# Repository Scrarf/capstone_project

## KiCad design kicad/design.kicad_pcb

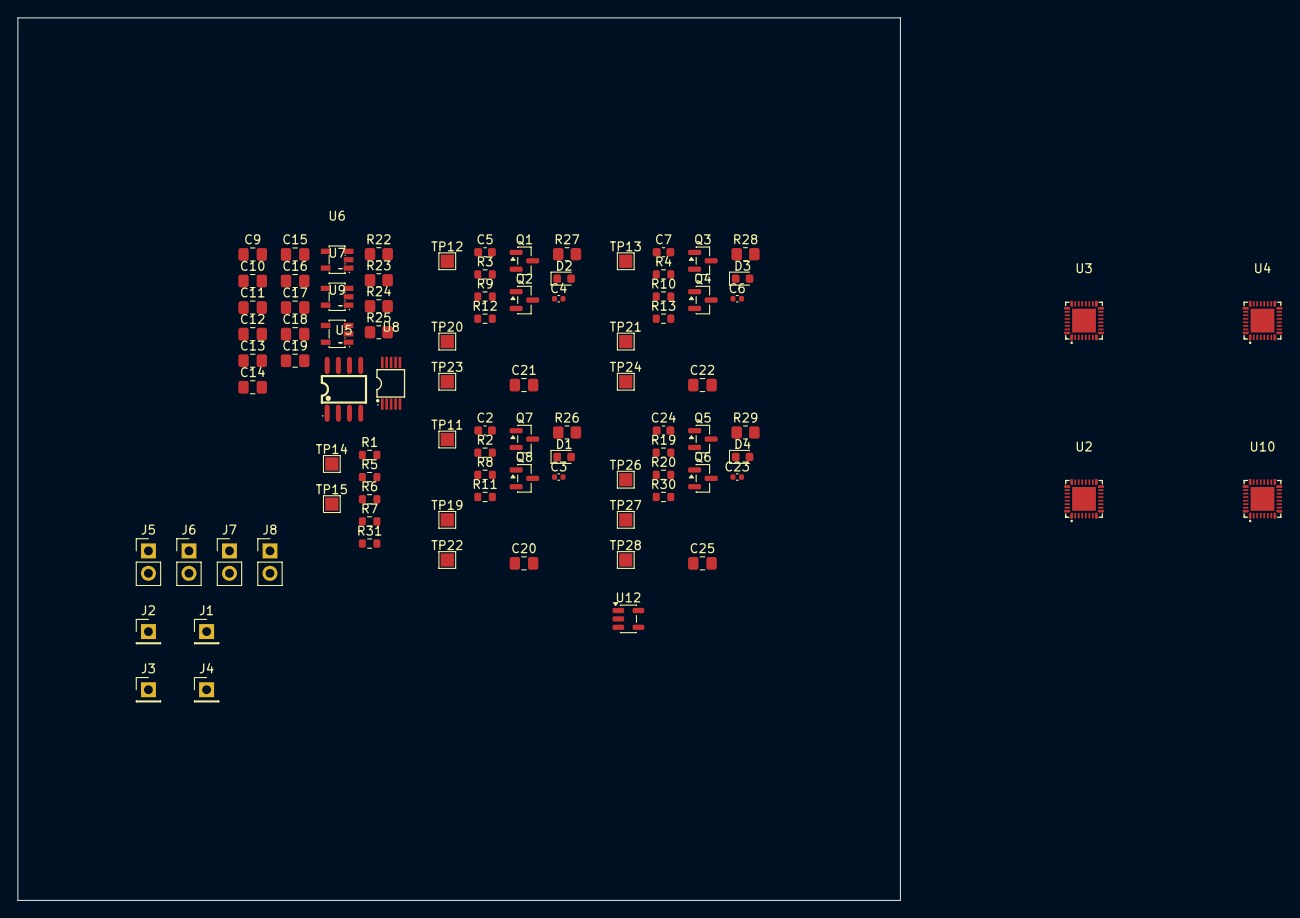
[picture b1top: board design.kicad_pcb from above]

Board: 2 copper layers, 100.0 x 100.0 mm, 92 parts (0 on the bottom side), 71 nets, no tracks yet.

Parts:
C2, C5, C7, C24: 4.7u; C_0603_1608Metric
C3, C4, C6, C23: 0.1u; C_0402_1005Metric
C9, C11, C12, C17, C20, C21, C22, C25: 1uF; C_0805_2012Metric_Pad1.18x1.45mm_HandSolder
C10: 10uF; C_0805_2012Metric_Pad1.18x1.45mm_HandSolder
C13: 4.7pF; C_0805_2012Metric_Pad1.18x1.45mm_HandSolder
C14, C15, C16, C18, C19: 100nF; C_0805_2012Metric_Pad1.18x1.45mm_HandSolder
D1, D2, D3, D4: LED; LED_0603_1608Metric
J1, J2, J3, J4: Conn_01x01; PinHeader_1x01_P2.54mm_Vertical
J5, J6, J7, J8: Conn_01x02; PinHeader_1x02_P2.54mm_Vertical
Q1, Q2, Q3, Q4, Q5, Q6, Q7, Q8: BSS138; SOT-23
R1, R6, R7, R31: 0; R_0603_1608Metric
R2, R3, R4, R20: 4.7k; R_0603_1608Metric
R5, R8, R9, R10, R30: 10k; R_0603_1608Metric
R11, R12, R13, R19: 470; R_0603_1608Metric
R22, R23, R25: 10K; R_0805_2012Metric_Pad1.20x1.40mm_HandSolder
R24: 36K; R_0805_2012Metric_Pad1.20x1.40mm_HandSolder
R26, R27, R28, R29: 100K; R_0805_2012Metric_Pad1.20x1.40mm_HandSolder
TP11, TP12, TP13, TP14, TP15, TP19, TP20, TP21, TP22, TP23, TP24, TP26, TP27, TP28: TestPoint; TestPoint_Pad_1.5x1.5mm
U2, U3, U4, U10: CH32L103K8U6; QFN-32_L4.0-W4.0-P0.40-BL-EP2.7-A
U5: REF5050AIDR; SOIC-8_L5.0-W4.0-P1.27-LS6.0-BL
U6, U7, U9: OPA197IDBVR; SOT-23-5_L3.0-W1.7-P0.95-LS2.8-BR
U8: DAC7811IDGSR; VSSOP-10_L3.0-W3.0-P0.50-LS4.9-BL
U12: OPA810xDBV; SOT-23-5

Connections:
+5V: C14.1, C15.1, C17.1, U6.5 (V+), U7.5 (V+)
+12V: C9.1, C18.1, C19.1, U5.2 (VIN), U9.5 (V+)
/3v3: C2.1, C3.1, C4.1, C5.1, C6.1, C7.1, C23.1, C24.1, TP14.1 (1_1), U2.1 (VDD), U3.1 (VDD), U4.1 (VDD), U10.1 (VDD)
/DAC/DAC_OUT: R24.2, U9.1
/DAC/VREF: C10.1, R22.1, U5.6 (VOUT), U8.9 (VREF)
/ELECTRODE1/0V_DAC: C21.2, R27.1
/ELECTRODE1/CLK_OUT: R7.2, U3.18 (PA8), U4.4 (OSC_IN/PD0)
/ELECTRODE1/SPI_MISO: R10.2, U3.27 (PB4), U4.28 (PB5)
/ELECTRODE1/SPI_SCK: R6.1, U3.26 (PB3)
/ELECTRODE1/SWCLK: J6.1, U3.24 (PA14/SWCLK)
/ELECTRODE1/SWDIO: J6.2, U3.23 (PA13/SWDIO)
/ELECTRODE2/0V_DAC: C22.2, R28.1
/ELECTRODE2/CLK_OUT: R31.2, U4.18 (PA8), U10.4 (OSC_IN/PD0)
/ELECTRODE2/SPI_MISO: R30.2, U4.27 (PB4), U10.28 (PB5)
/ELECTRODE2/SPI_SCK: R7.1, U4.26 (PB3)
/ELECTRODE2/SWCLK: J7.1, U4.24 (PA14/SWCLK)
/ELECTRODE2/SWDIO: J7.2, U4.23 (PA13/SWDIO)
/ELECTRODE3/0V_DAC: C25.2, R29.1
/ELECTRODE3/SPI_SCK: R31.1, U10.26 (PB3)
/ELECTRODE3/SWCLK: J8.1, U10.24 (PA14/SWCLK)
/ELECTRODE3/SWDIO: J8.2, U10.23 (PA13/SWDIO)
/ELECTRODE/0V_DAC: C20.2, R26.1
/ELECTRODE/CLK_IN: R1.2, U2.4 (OSC_IN/PD0)
/ELECTRODE/CLK_OUT: R6.2, U2.18 (PA8), U3.4 (OSC_IN/PD0)
/ELECTRODE/SPI_MISO: R9.2, U2.27 (PB4), U3.28 (PB5)
/ELECTRODE/SPI_MOSI: R8.2, U2.28 (PB5)
/ELECTRODE/SPI_SCK: R1.1, U2.26 (PB3)
/ELECTRODE/SWCLK: J5.1, U2.24 (PA14/SWCLK)
/ELECTRODE/SWDIO: J5.2, U2.23 (PA13/SWDIO)
/NSS: R5.1, TP15.1 (1_1), U2.25 (PA15), U3.25 (PA15), U4.25 (PA15), U10.25 (PA15)
GND: C2.2, C3.2, C4.2, C5.2, C6.2, C7.2, C9.2, C10.2, C11.2, C12.2, C14.2, C15.2, C16.2, C17.2, C18.2, C19.2, C23.2, C24.2, D1.1 (K), D2.1 (K), D3.1 (K), D4.1 (K), R2.1, R3.1, R4.1, R5.2, R8.1, R9.1, R10.1, R20.1, R23.2, R25.2, R26.2, R27.2, R28.2, R29.2, R30.1, TP11.1 (1_1), TP12.1 (1_1), TP13.1 (1_1), TP28.1 (1_1), U2.33 (EP), U3.33 (EP), U4.33 (EP), U5.4 (GND), U6.2 (V-), U7.2 (V-), U8.3 (GND), U9.2 (V-), U10.33 (EP), U12.2 (V-)
unnamed: D1.2 (A), R11.2
unnamed: D2.2 (A), R12.2
unnamed: D3.2 (A), R13.2
unnamed: D4.2 (A), R19.2
unnamed: J1.1 (Pin_1_1), U2.15 (PB1/ADC9)
unnamed: J2.1 (Pin_1_1), U3.15 (PB1/ADC9)
unnamed: J3.1 (Pin_1_1), U4.15 (PB1/ADC9)
unnamed: J4.1 (Pin_1_1), U10.15 (PB1/ADC9)
unnamed: Q1.1 (G), U3.21 (PA11/UDM)
unnamed: C21.1, Q1.2 (S)
unnamed: Q3.1 (G), U4.21 (PA11/UDM)
unnamed: C22.1, Q3.2 (S)
unnamed: Q5.1 (G), U10.21 (PA11/UDM)
unnamed: C25.1, Q5.2 (S)
unnamed: Q7.1 (G), U2.21 (PA11/UDM)
unnamed: C20.1, Q7.2 (S)
unnamed: R2.2, U2.31 (BOOT0/PB9)
unnamed: TP19.1 (1_1), U2.19 (PA9)
unnamed: TP22.1 (1_1), U2.20 (PA10)
unnamed: R11.1, U2.32 (PB8)
unnamed: R3.2, U3.31 (BOOT0/PB9)
unnamed: TP20.1 (1_1), U3.19 (PA9)
unnamed: TP23.1 (1_1), U3.20 (PA10)
unnamed: R12.1, U3.32 (PB8)
unnamed: R4.2, U4.31 (BOOT0/PB9)
unnamed: TP21.1 (1_1), U4.19 (PA9)
unnamed: TP24.1 (1_1), U4.20 (PA10)
unnamed: R13.1, U4.32 (PB8)
unnamed: C11.1, U5.5 (TRIMNR)
unnamed: C12.1, R22.2, R23.1, U6.3 (+)
unnamed: U6.1, U6.4 (-), U7.3 (+), U8.2 (IOUT2)
unnamed: C13.1, U7.4 (-), U8.1 (IOUT1)
unnamed: C13.2, U7.1, U8.10 (RFB), U9.3 (+)
unnamed: C16.1, U8.8 (VDD)
unnamed: R24.1, R25.1, U9.4 (-)
unnamed: R20.2, U10.31 (BOOT0/PB9)
unnamed: TP26.1 (1_1), U10.19 (PA9)
unnamed: TP27.1 (1_1), U10.20 (PA10)
unnamed: R19.1, U10.32 (PB8)
unnamed: U12.1, U12.4 (-)
